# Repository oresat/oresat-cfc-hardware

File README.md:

# oresat-cfc-hardware

Cirrrus Flux Camera hardware repository. See also https://www.oresat.org/satellites/oresat/mission-2-cfc.

## General information
The Cirrus Flux Camera (CFC) is a Short Wave Infrared (SWIR) camera meant to map the global distribution of high-altitude cirrus clouds. It works by looking at the reflected sunlight from clouds in three SWIR bands. The primary investigators (PIs) for CFC calibration, data processing, and climate science are our collaborators at the [University of Maryland Baltimore Count (UMBC)'s Earth and Space Institute (ESI)](https://esi.umbc.edu/) as well as by our collaborators at the [University College London (UCL) Mullard Space Science Laboratory (MSSL)](https://www.ucl.ac.uk/mathematical-physical-sciences/mssl).

Older versions of the CFC flew on the [2022 NASA High Altitude Student Payload (HASP)](https://sg-webserver.phys.lsu.edu/) mission.

Different but modern versions were flown by [UMBC's AirHARP mission](https://esi.umbc.edu/airharp2-at-pace-pax/) on the NASA ER-2 high altitude plane.

Most recently, we flew a preliminary technology demonstration mission on [OreSat0.5](https://www.oresat.org/satellites/oresat0-5) launched August 16th, 2024.

We're planning on flying the science mission camera on OreSat1 in Q2 2026.

Versions of the CFC have also flown on the NASA High Altitude Student Payload (HASP) in New Mexico, and 
## Technical information about the CFC sensor

- Princeton IR PIRT1280 InGaAs focal plane array (1280 x 1024 with 12 um pixels), sensitive to roughly 800 - 1600 nm.
- We cool the sensor to -8 deg C using its built-in thermal electric cooler (TEC - just a standard Peltier device).
- We use three filters on the PIRT1280 sensors:
   - 870 nm: [Torrent Photonics Optical Filter Shop 2020OFS-870](https://opticalfiltershop.com/shop/bandpass-filter/nir-bandpass-700nm-to-1100nm/nir-bandpass-filter-870nm-fwhm-30nm/)
   - 1390 nm: [Torrent Photonics Optical Filter Shop 2020OFS-1390](https://opticalfiltershop.com/shop/bandpass-filter/swir-bandpass-filters-1-1um-to-3-0um/swir-bandpass-filter-1390nm-fwhm-35nm/)
   - 1590 nm: [Torrent Photonics Optical Filter Shop 2020OFS-1590](https://opticalfiltershop.com/shop/bandpass-filter/swir-bandpass-filters-1-1um-to-3-0um/swir-bandpass-filter-1590nm-fwhm-40nm/)
- Lens is the [Navitar SWIR-35](https://store.navitar.com/swir-35-35-mm/), a 35 mm  SWIR lens with focus adjustable apateur. 

## Technical information on the system

- The **CFC Sensor Card** is a PCB in backplane slot 18. It has:
   - The PIRT 1280 sensor soldered on the PCB
   - A custom machined lens adapter between the card and the lens.
   - Custom machined G10 L brackets between the custom machined lens adapter and slot 19 
   - The lens on the adapter sticks through the -Z end card, through the -Z end cap, and finally out into the tuna can volume. A 3D printed adapter on the End Card holds the monopole deployers and holds the camera lens at the End Card and End Cap levels.
   - The SWIR lens sticks into the tuna-can space on the -Z end of OreSat0.5 and OreSat1.
- The **CFC Processor Card** is a PCB in backplane slot 17 with:
   - LVDS to PRU adapter IC
   - an [Octavo OSD335x-SM](https://octavosystems.com/octavo_products/osd335x-sm/) system in package (SIP) processor with 1 GB DRAM and a 16 GB eMMC storage IC.
 - Radiator
    - The top of the CFC Sensor Card has a large block of copper being used as a heat spreader. The heat spreader dumps the heat from the TEC into thin copper leaf springs that lead the heat to two external copper radiators in the -Z+Y and -Z-Y solar module positions. These copper radiators are covered by a high emissivity tape.
    
## Design Notes

- Mostly on our Google Drive right now, here's the beginnings of our [CFC Design Notes](https://docs.google.com/document/d/1nDrTuUim9k1om3DOcBtnp3ixVvrmmALAsb2CZlDwwio/edit?usp=sharing).

## Links to CAD

- [OreSat CFC Camera mechnical in OnShape](https://cad.onshape.com/documents/0e986a82427039a7549eafca/v/f54f3484c685a75ab5bd82ce/e/deddd282159689e0e52f600b)
- [OreSat0.5 containing the CFC assembly in OnShape](https://cad.onshape.com/documents/c0a6cf3367d8fdcad3a3c2e1/w/ca55e3ec6f041493d70e4b39/e/591851cdc8c634aae1522f90)
- [Electronics CAD on Github](https://github.com/oresat/oresat-cfc-hardware) - mostly KiCad with some older EAGLE files.
- [Kernel module](https://github.com/oresat/oresat-prucam-pirt1280) for the PIRT 1280 on the Octavo's PRU.

## License

All materials in this repo are copyright Portland State Aerospace Society and are licensed under the CERN Open Hardware Licence Version 2 -
Strongly Reciprocal (CERN-OHL-S v2), or any later version. A copy of the license is located in [here](LICENSE.md).

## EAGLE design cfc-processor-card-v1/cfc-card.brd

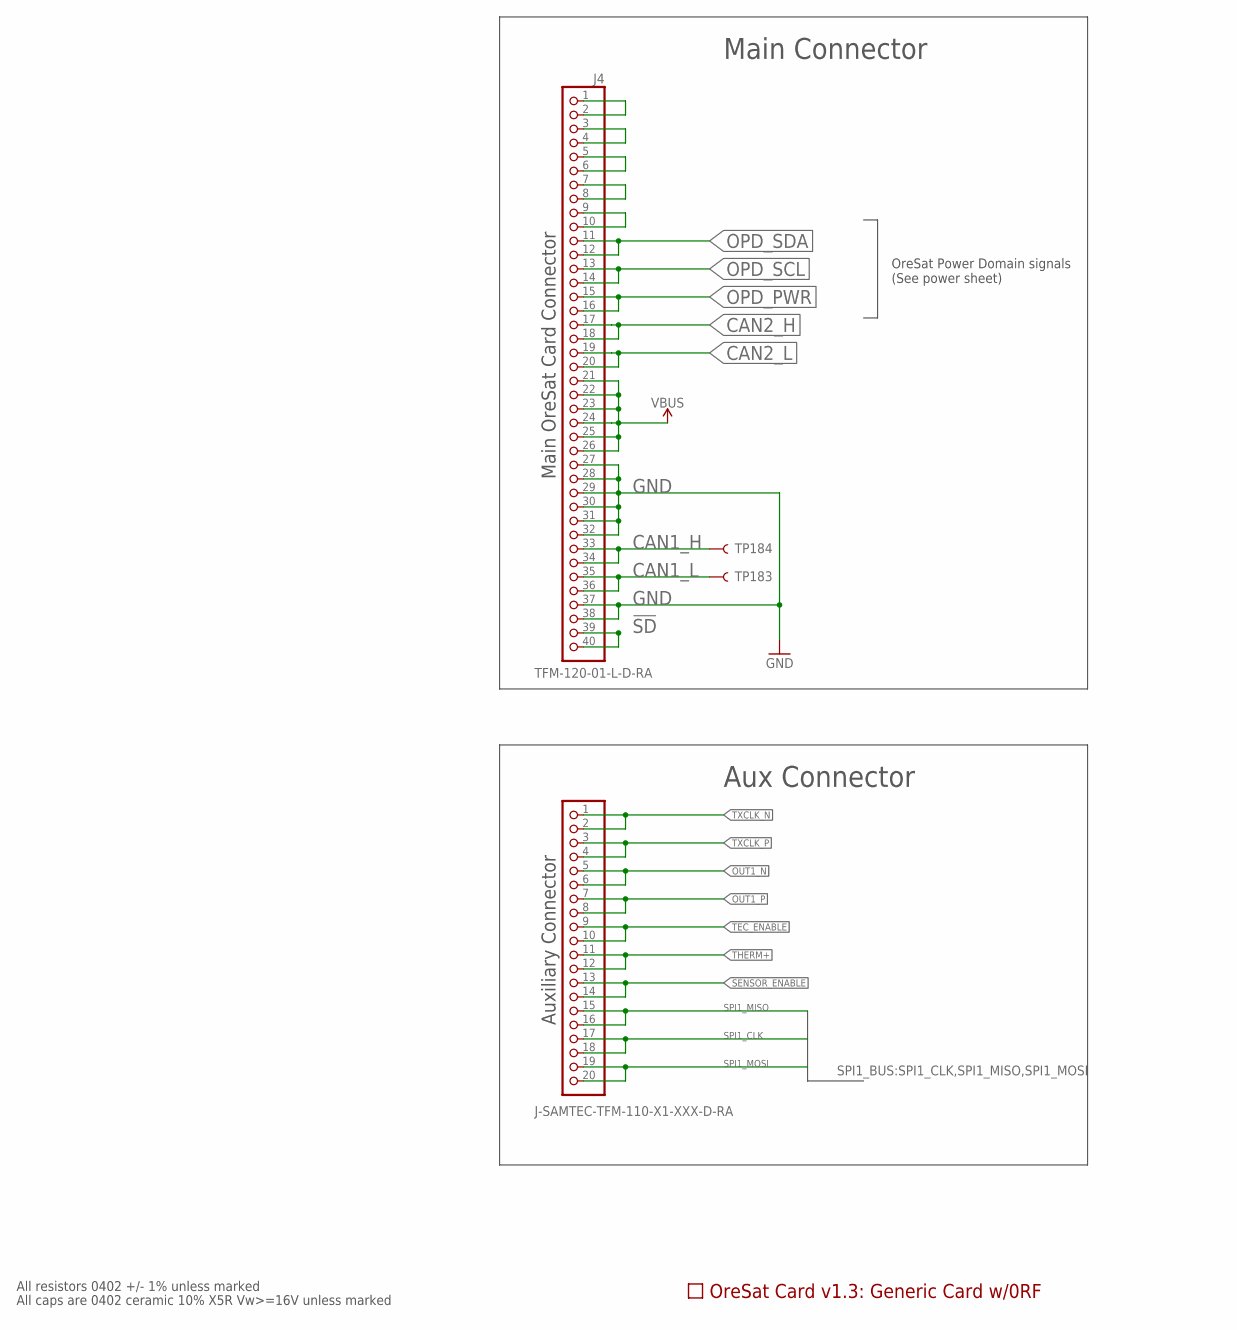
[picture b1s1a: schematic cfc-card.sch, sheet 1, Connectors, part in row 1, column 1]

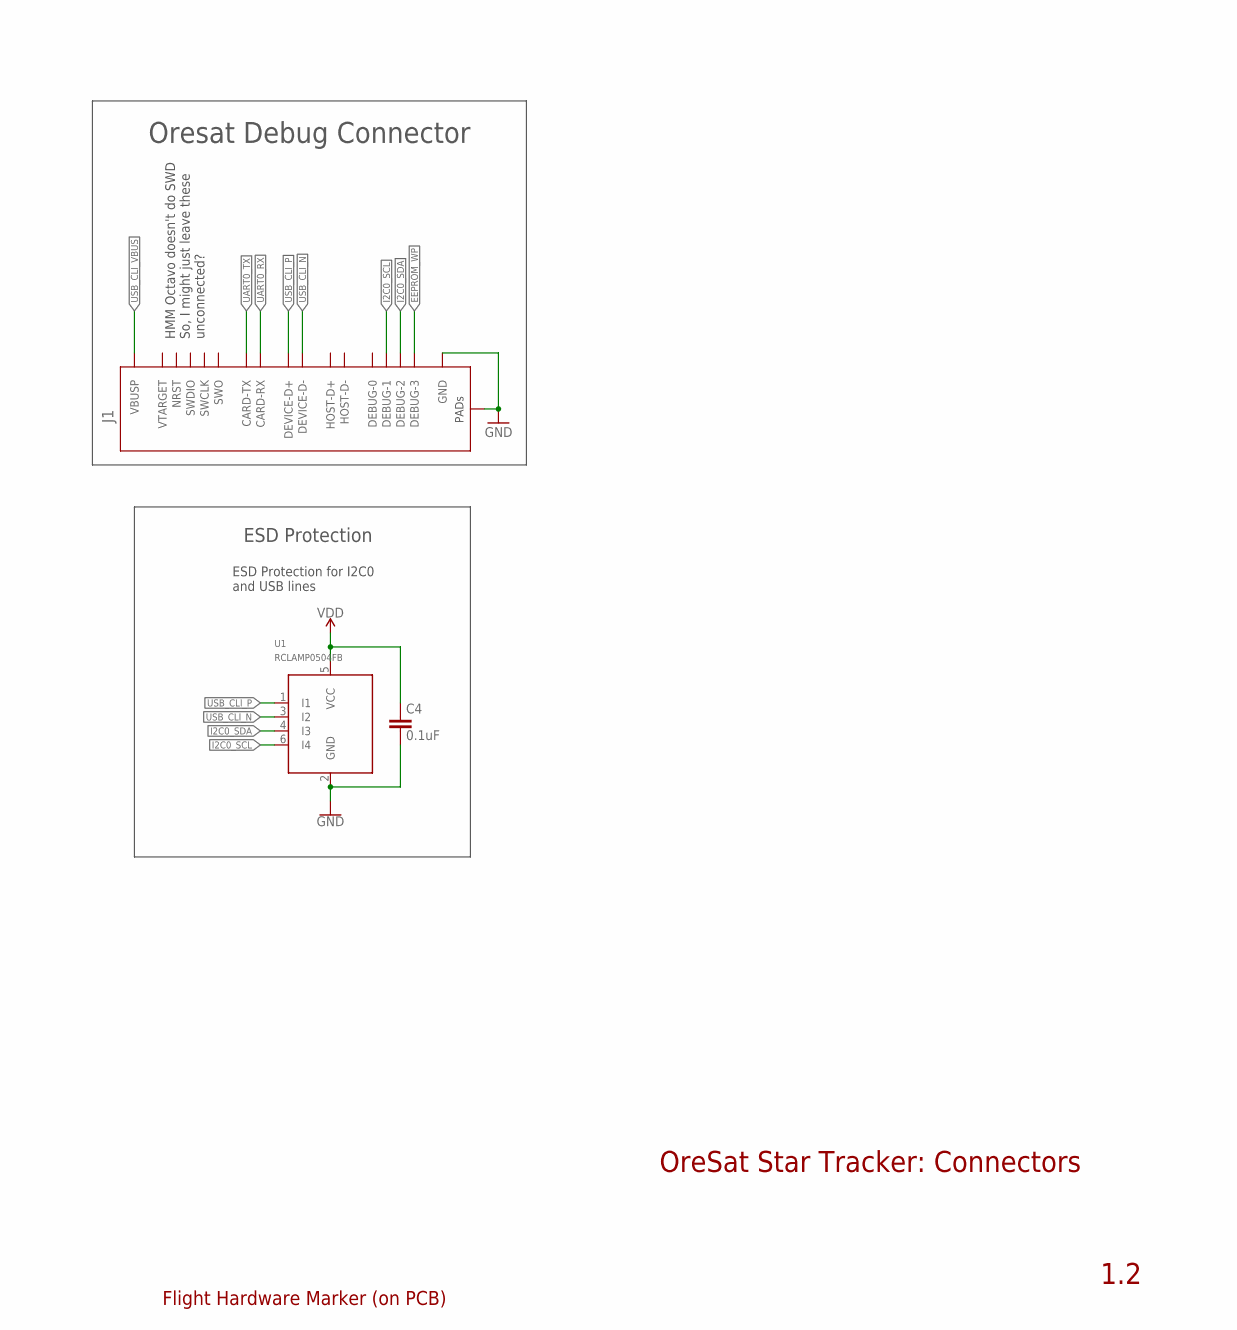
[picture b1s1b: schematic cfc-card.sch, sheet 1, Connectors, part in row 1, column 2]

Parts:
C4: 0.1uF; .0603-A
J1: ORESAT-DEBUG-CONNECTOR-ALL; TE_2-1734592-0
J2: J-SAMTEC-TFM-110-X1-XXX-D-RA; MPN TFM-110-01-L-D-RA
J4: TFM-120-01-L-D-RA; J-SAMTEC-TFM-120-X1-XXX-D-RA
PCB1: ORESAT-CARD-V1.3-GENERIC-0RF
TP183, TP184: TEST-POINT3X4; PAD.03X.04
U1: RCLAMP0504FB; SC70-6
U$1: FLIGHMARKERNEW; FLIGHTMARKER_NEW_BOARDS

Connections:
!SD: J4.39, J4.40
CAN1_H: J4.33, J4.34, TP184.P$1
CAN1_L: J4.35, J4.36, TP183.P$1
CAN2_H: J4.17, J4.18; also elsewhere on the board
CAN2_L: J4.19, J4.20; also elsewhere on the board
EEPROM_WP: J1.20 (DEBUG-3); also elsewhere on the board
GND: C4.2, J1.3 (GND), J1.6 (GND), J1.9 (GND), J1.PAD1 (PAD), J1.PAD2 (PAD), J4.27, J4.28, J4.29, J4.30, J4.31, J4.32, J4.37, J4.38, U1.2 (GND); also elsewhere on the board
I2C0_SCL: J1.18 (DEBUG-1), U1.6 (I4); also elsewhere on the board
I2C0_SDA: J1.19 (DEBUG-2), U1.4 (I3); also elsewhere on the board
unnamed: J4.1, J4.2
OPD_PWR: J4.15, J4.16; also elsewhere on the board
OPD_SCL: J4.13, J4.14; also elsewhere on the board
OPD_SDA: J4.11, J4.12; also elsewhere on the board
OUT1_N: J2.5, J2.6; also elsewhere on the board
OUT1_P: J2.7, J2.8; also elsewhere on the board
SENSOR_ENABLE: J2.13, J2.14; also elsewhere on the board
SPARE1: J4.9, J4.10
SPARE2: J4.7, J4.8
SPARE3: J4.5, J4.6
SPARE4: J4.3, J4.4
SPI1_CLK: J2.17, J2.18; also elsewhere on the board
SPI1_MISO: J2.15, J2.16; also elsewhere on the board
SPI1_MOSI: J2.19, J2.20; also elsewhere on the board
TEC_ENABLE: J2.9, J2.10; also elsewhere on the board
THERM+: J2.11, J2.12; also elsewhere on the board
TXCLK_N: J2.1, J2.2; also elsewhere on the board
TXCLK_P: J2.3, J2.4; also elsewhere on the board
UART0_RX: J1.12 (CARD-RX); also elsewhere on the board
UART0_TX: J1.13 (CARD-TX); also elsewhere on the board
USB_CLI_N: J1.5 (DEVICE-D-), U1.3 (I2); also elsewhere on the board
USB_CLI_P: J1.4 (DEVICE-D+), U1.1 (I1); also elsewhere on the board
USB_CLI_VBUS: J1.1 (VBUSP), J1.2 (VBUSP); also elsewhere on the board
VBUS: J4.21, J4.22, J4.23, J4.24, J4.25, J4.26; also elsewhere on the board
VDD: C4.1, U1.5 (VCC); also elsewhere on the board

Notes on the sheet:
OreSat Star Tracker: Connectors
1.2
All resistors 0402 +/- 1% unless marked
All caps are 0402 ceramic 10% X5R Vw>=16V unless marked
Main Connector
Main OreSat Card Connector
OreSat Power Domain signals (See power sheet)
HMM Octavo doesn't do SWD So, I might just leave these unconnected?
Oresat Debug Connector
Auxiliary Connector
Aux Connector
ESD Protection for I2C0 and USB lines
ESD Protection

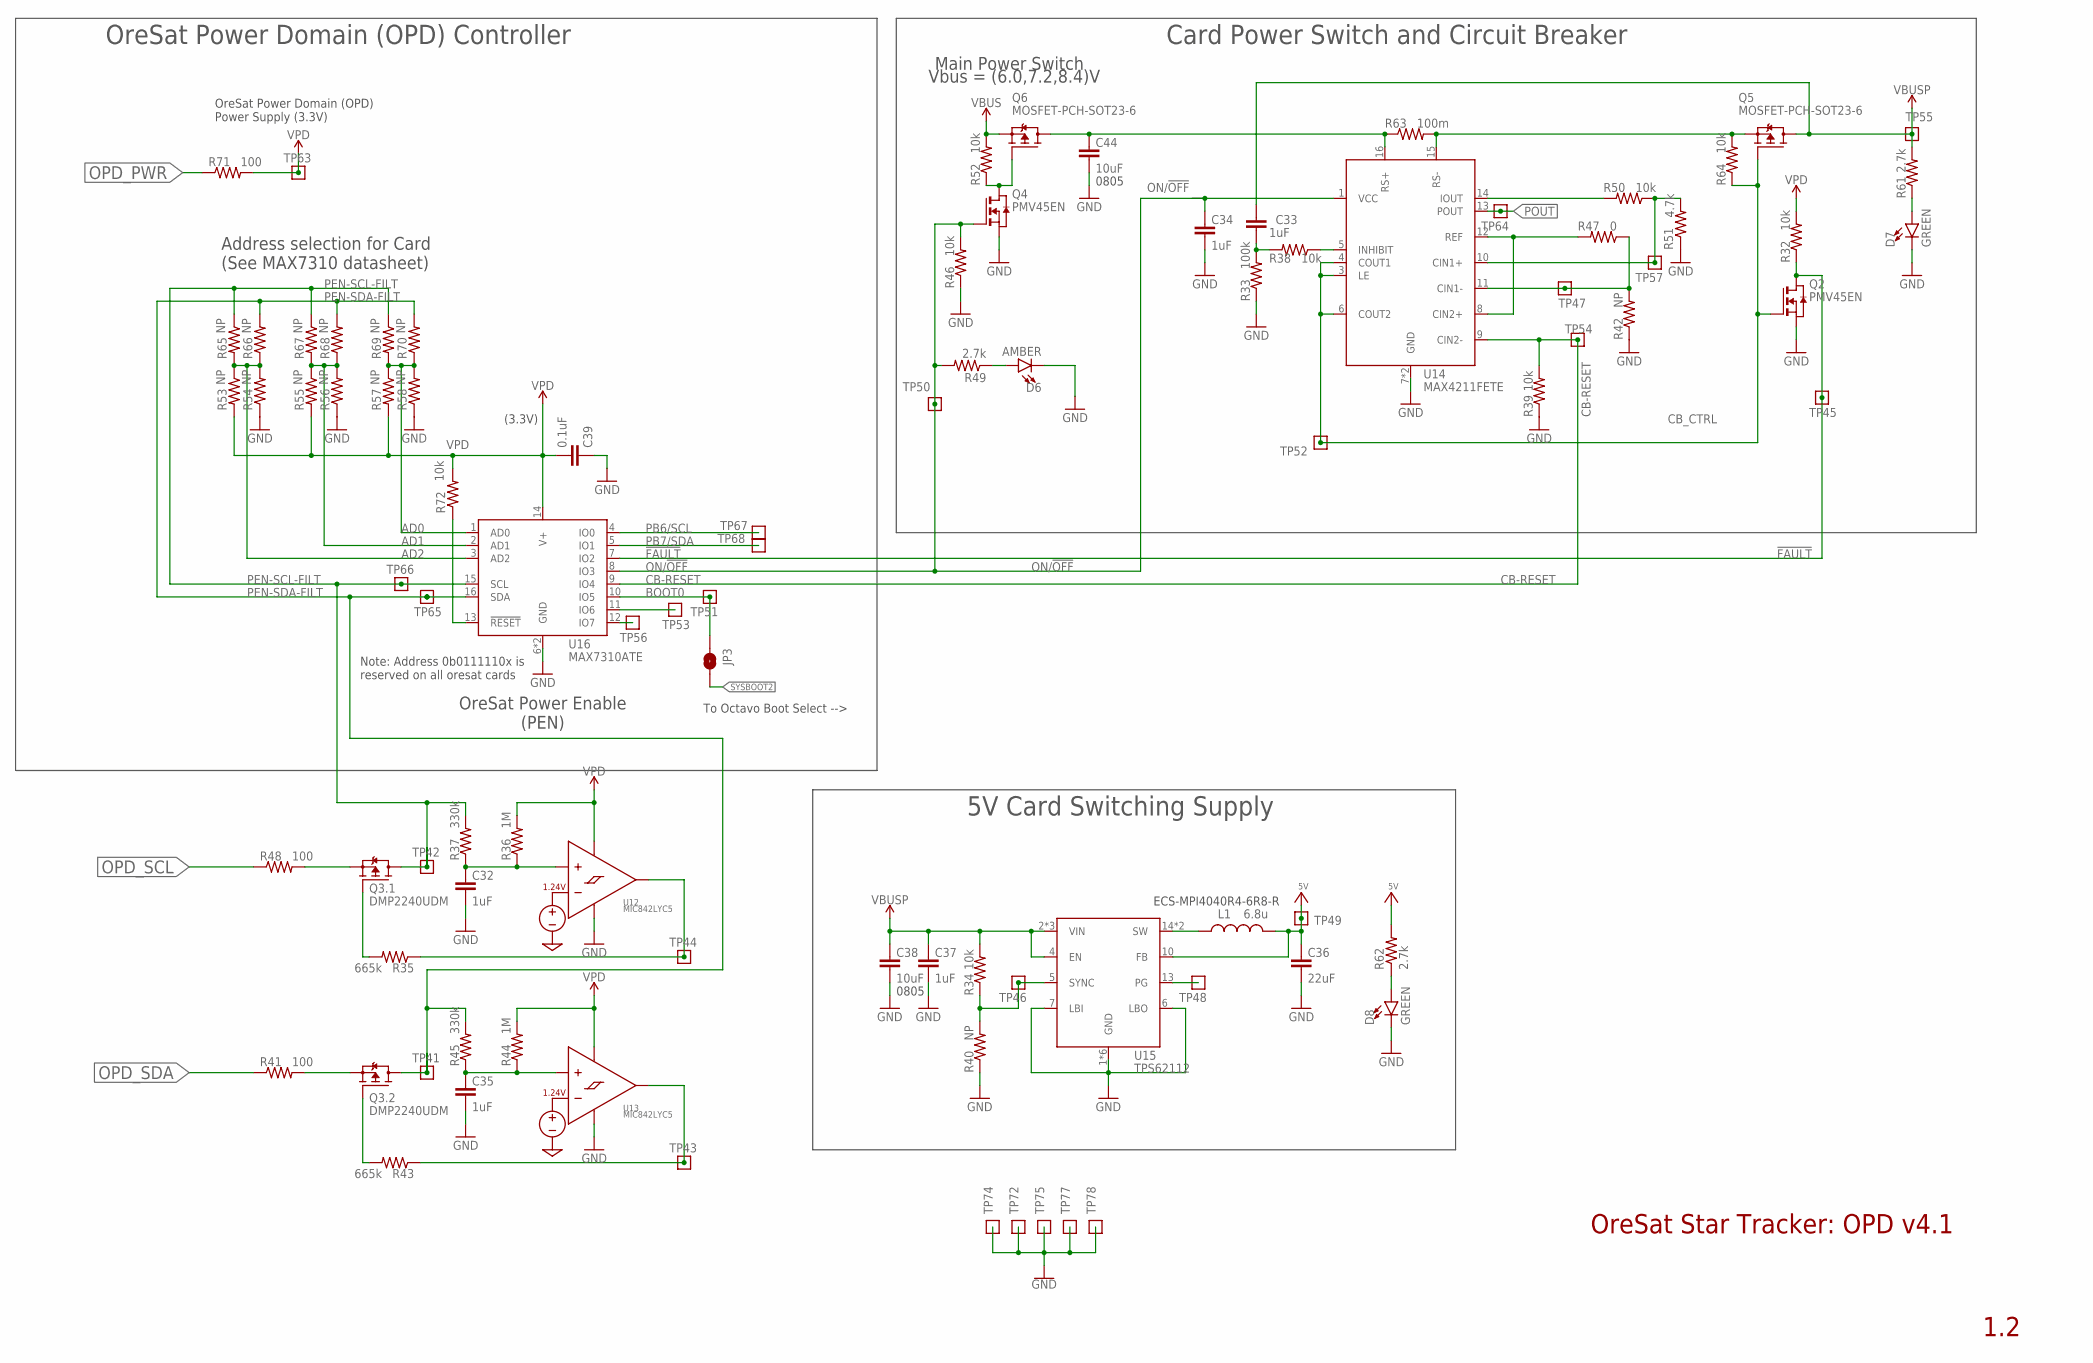
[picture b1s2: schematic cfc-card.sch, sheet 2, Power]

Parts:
C32, C35: 1uF; .0805-B-NOSILK
C33, C34, C37: 1uF; .0603-A
C36: 22uF; C1210
C38, C44: 10uF; .0805-B
C39: 0.1uF; .0603-A
D6: AMBER; LED-0603
D7, D8: GREEN; LED-0603
JP3: JUMPER-SMT_2_NO_SILK; SMT-JUMPER_2_NO_SILK
L1: 6.8u; ECS-MPI4040
Q2, Q4: PMV45EN; SOT23; MPN PMV45EN2R
Q3: DMP2240UDM; SOT23-6
Q5, Q6: MOSFET-PCH-SOT23-6; SOT23-6; MPN DMP3050LVT-7
R32, R34, R39, R46, R50, R52, R64, R72: 10k; .0603-A
R33: 100k; .0603-A; MPN RC1005F6653CS
R35, R43: 665k; .0603-A
R36, R44: 1M; .0603-A
R37, R45: 330k; .0603-A
R38: 10k; .0603-A; MPN RC1005F6653CS
R40, R42, R53, R54, R55, R56, R57, R58, R65, R66, R67, R68, R69, R70: NP; .0603-A; MPN RC1005F6653CS
R41, R48, R71: 100; .0603-A
R47: 0; .0603-A
R49, R61, R62: 2.7k; .0603-A
R51: 4.7k; .0603-A; MPN RC1005F6653CS
R63: 100m; R1206
TP41, TP42, TP43, TP44, TP45, TP46, TP47, TP48, TP49, TP50, TP51, TP52, TP53, TP54, TP55, TP56, TP57, TP63, TP64, TP65, TP66, TP67, TP68, TP72, TP74, TP75, TP77, TP78: TEST-POINT; 2MM-TEST-POINT
U12, U13: MIC842LYC5; SC70-5
U14: MAX4211FETE; QFN65P400X400X80-17T210
U15: TPS62112; S-PVQFN-16
U16: MAX7310ATE; QFN65P400X400X80-17T210; MPN MAX7310ATE

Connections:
5V: C36.1, L1.2, R62.2, TP49.1, U15.10 (FB); also elsewhere on the board
!FAULT: Q2.3 (D), R32.1, TP45.1, U16.7 (IO2)
AD0: R57.1, R58.2, R69.2, R70.1, U16.1 (AD0)
AD1: R55.1, R56.2, R67.2, R68.1, U16.2 (AD1)
AD2: R53.1, R54.2, R65.2, R66.1, U16.3 (AD2)
BOOT0: JP3.1, TP51.1, U16.10 (IO5)
CB-RESET: R39.2, TP54.1, U14.9 (CIN2-), U16.9 (IO4)
CB_CTRL: Q2.1 (G), Q5.3 (G), R64.1, TP52.1, U14.3 (LE), U14.4 (COUT1), U14.6 (COUT2)
GND: C32.2, C34.2, C35.2, C36.2, C37.2, C38.2, C39.1, C44.2, D6.C, D7.C, D8.C, Q2.2 (S), Q4.2 (S), R33.1, R39.1, R40.1, R42.1, R46.1, R51.1, R54.1, R56.1, R58.1, TP72.1, TP74.1, TP75.1, TP77.1, TP78.1, U12.2 (GND), U13.2 (GND), U14.7 (GND), U14.EPAD (GND), U15.1 (GND), U15.6 (LBO), U15.7 (LBI), U15.9 (GND), U15.11 (GND), U15.12 (GND), U15.16 (GND), U15.PAD (GND), U16.6 (GND), U16.EPAD (GND); also elsewhere on the board
IOUT: R50.2, U14.14 (IOUT)
unnamed: C32.1, R36.1, R37.1, U12.1 (INP)
unnamed: R35.1, TP44.1, U12.4 (OUT)
unnamed: TP56.1, U16.12 (IO7)
unnamed: C44.1, Q6.1 (D), Q6.2 (D), Q6.5 (D), Q6.6 (D), R63.1, U14.16 (RS+)
unnamed: Q5.4 (S), R63.2, R64.2, U14.15 (RS-)
unnamed: C35.1, R44.1, R45.1, U13.1 (INP)
unnamed: Q3.3 (G), R43.2
unnamed: Q3.1 (G), R35.2
unnamed: D7.A, R61.1
unnamed: D8.A, R62.1
unnamed: TP53.1, U16.11 (IO6)
unnamed: Q3.5 (S), R48.2
unnamed: D6.A, R49.1
unnamed: Q3.2 (S), R41.2
unnamed: R43.1, TP43.1, U13.4 (OUT)
unnamed: R72.1, U16.13 (!RESET)
unnamed: Q4.3 (D), Q6.3 (G), R52.1
unnamed: R50.1, R51.2, TP57.1, U14.10 (CIN1+)
unnamed: R42.2, R47.1, TP47.1, U14.11 (CIN1-)
unnamed: R47.2, U14.8 (CIN2+), U14.12 (REF)
unnamed: C33.1, R33.2, R38.2
unnamed: R38.1, U14.5 (INHIBIT)
ON/!OFF: C34.1, Q4.1 (G), R46.2, R49.2, TP50.1, U14.1 (VCC), U16.8 (IO3)
OPD_PWR: R71.1; also elsewhere on the board
OPD_SCL: R48.1; also elsewhere on the board
OPD_SDA: R41.1; also elsewhere on the board
PB6/SCL: TP67.1, U16.4 (IO0)
PB7/SDA: TP68.1, U16.5 (IO1)
PEN-SCL-FILT: Q3.6 (D), R37.2, R65.1, R67.1, R69.1, TP42.1, TP66.1, U16.15 (SCL)
PEN-SDA-FILT: Q3.4 (D), R45.2, R66.2, R68.2, R70.2, TP41.1, TP65.1, U16.16 (SDA)
POUT: TP64.1, U14.13 (POUT)
SYSBOOT2: JP3.2; also elsewhere on the board
TPS62111-PG: TP48.1, U15.13 (PG)
TPS62111-SYNC: R34.1, R40.2, TP46.1, U15.5 (SYNC)
TPS62111_SW: L1.1, U15.14 (SW), U15.15 (SW)
VBUS: Q6.4 (S), R52.2; also elsewhere on the board
VBUSP: C33.2, C37.1, C38.1, Q5.1 (D), Q5.2 (D), Q5.5 (D), Q5.6 (D), R34.2, R61.2, TP55.1, U15.2 (VIN), U15.3 (VIN), U15.4 (EN), U15.8 (VIN)
VPD: C39.2, R32.2, R36.2, R44.2, R53.2, R55.2, R57.2, R71.2, R72.2, TP63.1, U12.5 (VDD), U13.5 (VDD), U16.14 (V+)

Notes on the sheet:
0805
ECS-MPI4040R4-6R8-R
5V Card Switching Supply
1.2
Main Power Switch
OreSat Power Enable (PEN)
Address selection for Card (See MAX7310 datasheet)
(3.3V)
Vbus = (6.0,7.2,8.4)V
OreSat Power Domain (OPD) Power Supply (3.3V)
OreSat Power Domain (OPD) Controller
Card Power Switch and Circuit Breaker
Note: Address 0b0111110x is reserved on all oresat cards
OreSat Star Tracker: OPD v4.1
To Octavo Boot Select -->

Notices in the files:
parts and their libraries:
SparkFun-Connectors: Licensing: Creative Commons ShareAlike 4.0 International - https://creativecommons.org/licenses/by-sa/4.0
